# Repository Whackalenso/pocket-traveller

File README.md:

# Pocket Traveller

This is a Tamagotchi-inspired gadget to keep in your backpack, on your keychain, or in your pocket that encourages you to move more throughout your day.

The primary feature of the device is a screen that displays an avatar named Milo. Milo will walk when you walk, rest when you're idle, and sleep during long periods of inactivity. Milo will gain **XP** the more he moves, filling up a bar at the top of the screen. When this bar fills, Milo will gain a **level**. In addition to **level**, Milo will also become a **chud**, **plebian**, or **nomad** dependent on how much he has moved in the past few days. *Skip to [Interface Design and Art](#5-interface-design-and-art) for more details*

> *The name Milo comes from the famous ancient Greek athlete, Milo of Croton. Legend has it that he would lift a newborn ox on his shoulders every day, and as the ox grew bigger, so would he. In the same way, Milo's level and state is dependent on you, as if you were the ox.*

## Hardware

* **Raspberry Pi Pico** - The brain. Reads data from the motion sensor and controls the screen.
* **SH1106** - 1.3" OLED display.
* **ADXL345** - Accelerometer. Detects instantaneous acceleration that is used to estimate longer-term motion.
* **TPU4056** - Charger module. Provides the USB-C port for charging the battery.
* **3.7v 1000mAh Lipo Battery**

All electronic components are wired together on a perfboard which is housed inside of a 3D printed case.

## Process

### 1. Breadboard Proof of Concept

#### Hardware Testing
To begin, we connected the screen and motion sensor to the Pico on a breadboard to test whether they worked properly and to figure out how to interface with them. We had some trouble finding the correct address for interfacing with our motion sensor. We got it to work eventually but ended up having to replace the sensor because it was a knockoff.

#### Motion Data Classification Experiment
The next thing we needed to test is whether we could accurately classify data from the accelerometer into two states: idle and moving. This would be the core mechanism of the device, where everything else is just essentially an just interface to wrap around it. We knew this might be difficult because we chose our motion sensors to just be an accelerometer for simplicity, not an accelerometer + GPS combo. This means that the device has no reference for changes in position, only forces acted upon the device at each moment. 

After doing some research we learned that two qualities of the data can be measured in order to detect whether the user is moving: 

**Energy:** How strongly the device is moving. Measured as population variance of the magnitude of the force acted upon the sensor in a given window.<br>
**Rhythm:** How rhythmic the movements in the device are. Measured as how accurately a sequence of movements lines up with a shifted copy of itself.

The importance of this rhythm quality is that some movements may involve a lot of movement, such as shaking the device around or putting it into your backpack, however these movements shouldn't be classified as "moving". Actual "moving" scenarios, such as walking or running, will have a certain rhythm to it, as steps happen at a certain relative frequency.

Given all this, we needed to come up with thresholds for these two qualities in order to distinguish between moving and idle in a given time window. First, we made a sketch for the device that would simply display "IDLE" if the wearer is idle and "MOVING" if the wearer is moving. We played around with different values for the thresholds to see if we could create a result that seemed accurate. However, none of them seemed to work. So, abandoned trial and error and made a system to calibrate these thresholds:
1. Came up with a list of all possible movement scenarios that each give different kinds of data: sitting still, standing, fidgeting, slow walking, walking, running, and driving. Sitting still, standing, fidgeting, and driving would be classified as idle, while slow walking, walking, and running would be classified as moving. The hope/hypothesis was that there should be some value for both energy and rhythm that would separate one group from the other.
2. Created a Pico sketch for collecting energy and rhythm data
3. Recorded data for each scenario by performing the actions while holding the device
4. Created a Python script that plotted out all the data on a graph and automatically recommended thresholds for both qualities

*Recording running and driving data*

https://github.com/user-attachments/assets/422ddd09-90e0-466a-b9c1-0ad0e3300164

What we found was that the data reflected some of what we hoped: there is a clear distinction between the energy (variance) measured in "moving" states (shown in green) vs the energy measured in "idle" states. However, after looking at the graph on the right, we realized that rhythm was not necessary for distinguishing between moving and idle states, because the differences in energy alone already distinguished them. In addition, the recommended thresholds the script gave us were way off from what we observed in the graph. This didn't matter as much because we were able to look at the graph for ourselves and see where the line should be drawn, but it meant that something was off with our code and we would revisit it if needed.

We tried out our testing sketch again, but this time used 10^8 as our energy threshold and 0 for our rhythm threshold. This time, it was pretty reasonable at displaying "MOVING" when we moved with the device. However, since we weren't classifying the state with rhythm anymore, movements such as fidgeting shaking the device caused "MOVING" to be displayed as well. Our verdict was that this was good enough for now. As long as the device detects a moving state when the user is moving, it's ok that it doesn't perfectly detect and idle state. Random extra detected movement detected throughout the day will be insignificant compared to the actual long-term movement the user will actually do. The only downside is that the user may see the avatar on the screen move a little bit every now and then when they are just fidgeting with it. This will be something to revisit in the future when we have time to dive deeper into the calibration and data classification experiment.

#### Battery and Power States Proof of Concept

The next step was to test powering the device with a battery. There were a few new problems we needed to tackle:
Making sure the Pico doesn’t get damaged
Detecting that the device is being charged so that it can draw less power during this state and display a different screen
Adding a sleep state so that we can lengthen the battery life of the device without having an off button

After doing some research, we learned that routing the power from the battery through a schottkey diode was most optimal so that the charger module doesn’t get confused when detecting when the battery is full. We wired this up and the Pico didn’t blow up.

Next, we needed a way to detect whether the battery is currently being charged or not. Unfortunately, there was no dedicated pin for this on the TP4056 module. Our solution was to wire the input voltage signal– the voltage being received by the charging port– to a pin on the Pico. We had to use a voltage divider to transform this 5V signal into a 3.3V signal safe for the Pico. When this pin is read as high, we programmed the device to both draw less power (drawing power while charging the battery would confuse the charger module) and display “charging” text on the screen.

Finally, we programmed the device to go into “deep sleep” after a certain duration of inactivity. Because we chose to not have a power button on the device for simplicity, we needed a way for the device to turn off so that the battery doesn’t drain 24/7. This deep sleep state essentially powers off the Pico almost entirely. In order to wake the device up again, a special pin on the motion sensor that turns on when it detects motion can wake up the Pico even when it’s barely running.

### 3. Soldering Onto Perfboard

Now that the proof of concept was fleshed out, we could move on to soldering all the components into a more permanent and compact form that would be the innards of our final version. We began by creating a schematic in KiCad which was useful in guiding us to creating the most compact layout. Exact measurements were taken for each component to ensure our planned layout in the PCB editor was accurately spaced. This was important, especially making sure room was left for our wiring to run through the empty space in the board. Multiple wires and traces ran under components and through the back of the board, so any mistakes would be very hard to fix. Consequently, we made sure KiCad was referenced before soldering in any connections or components. Once everything was soldered in, we tested the code to make sure it ran properly. Much to our shock everything worked, so we taped down the battery to the board, trimmed the edges of the perfboard to get as compact of a design as possible and then moved on to designing the case. 

### 4. Designing a Case

Creating a case to house our circuit board was pretty straightforward:
* Measured all the components precisely with a caliper and/or looking at datasheets.
* Modeled the dimensions of the board and electronic components in CAD
* Modeled a box in two parts, the floor and everything else, to fit around the components. This included cutouts for the screen and USB port.
* Added a standoff on both the floor and box for one screw to screw from the floor through the circuit board into the box.
* Added fillets for aesthetics.
* Added tolerances for fit.
* Added a ring at the top so that the device can be used as a keychain

### 5. Interface Design and Art

There are four main features of the user interface that make up what this device is all about: the avatar, the level, the status, and the dialogues.

#### Avatar

The avatar is the defining feature of the device. It is an animation of Milo, our made up character. The drawing style is inspired by 16x16 pixel art Tamagotchi sprites. We drew each frame ourselves using pixel art software, then used a custom Python script, gen_sprites.py, to turn each image into data readable by the Pico, stored in sprites.h. For each status, there is an animation for resting and walking.

#### Level

The level is one of the two “movement-encouraging” features. It is is reflective of your total activity in the history of owning the device: it never goes down, only up. Whenever you move, you gain XP. Once you get a certain amount of XP, you will go up one level. Your level is displayed at the top of the screen. This XP value is hidden, however, a bar below the level indicator will fill up to reflect your progress towards the next level. Each level takes more and more XP to unlock, according to a formula such that level 10 is achievable in one week and level 100 is achievable in one year.

#### Status

The status is the second “movement-encouraging” feature. It is different from level in that it reflects how much you have been moving recently, as opposed to of all time. There are three statuses, “chud”, “pleb”, and “nomad”. The status indicator next to the level indicator will display one of these statuses depending on how much time in the past 72 hours you have spent moving. The current pace for each status are as follows:

Chud: <40 mins / day<br>
Pleb: ~1hr / day<br>
Nomad: >3hr / day

The threshold for promoting to a higher status is different than the threshold for demoting down to a lower rank so that sitting on the border between two statuses doesn’t cause weird issues. 

In addition to displaying your status at the top of the screen, Milo will also look different based on status:

| | Chud | Pleb | Nomad |
| :---: | :---:  | :---:  | :---:   |
| **Rest** | |  |  |
| **Walk** | |  |  |

#### Dialogues

The dialogues are a feature intended to add a little more whimsy, mystery, and sometimes encouragement to the device. After a long enough period of inactivity, picking up the device will cause text to pop up on the screen saying something about what Milo is doing or thinking about. These dialogues are stored in card_lines.h. Here are some examples:

*"milo is reading feminist literature"*<br>
*"milo is workshopping his memoir"*<br>
*"milo wants to go on a hike"*<br>
*"milo is getting into lifting to get over his boredom"*

Mostly these will just be jokes, however, they are intended to also subtly hint the user towards ways they can find more fulfillment in their own life. 

---

Made with ❤️ by Nigel Weiss and Brenden Cech

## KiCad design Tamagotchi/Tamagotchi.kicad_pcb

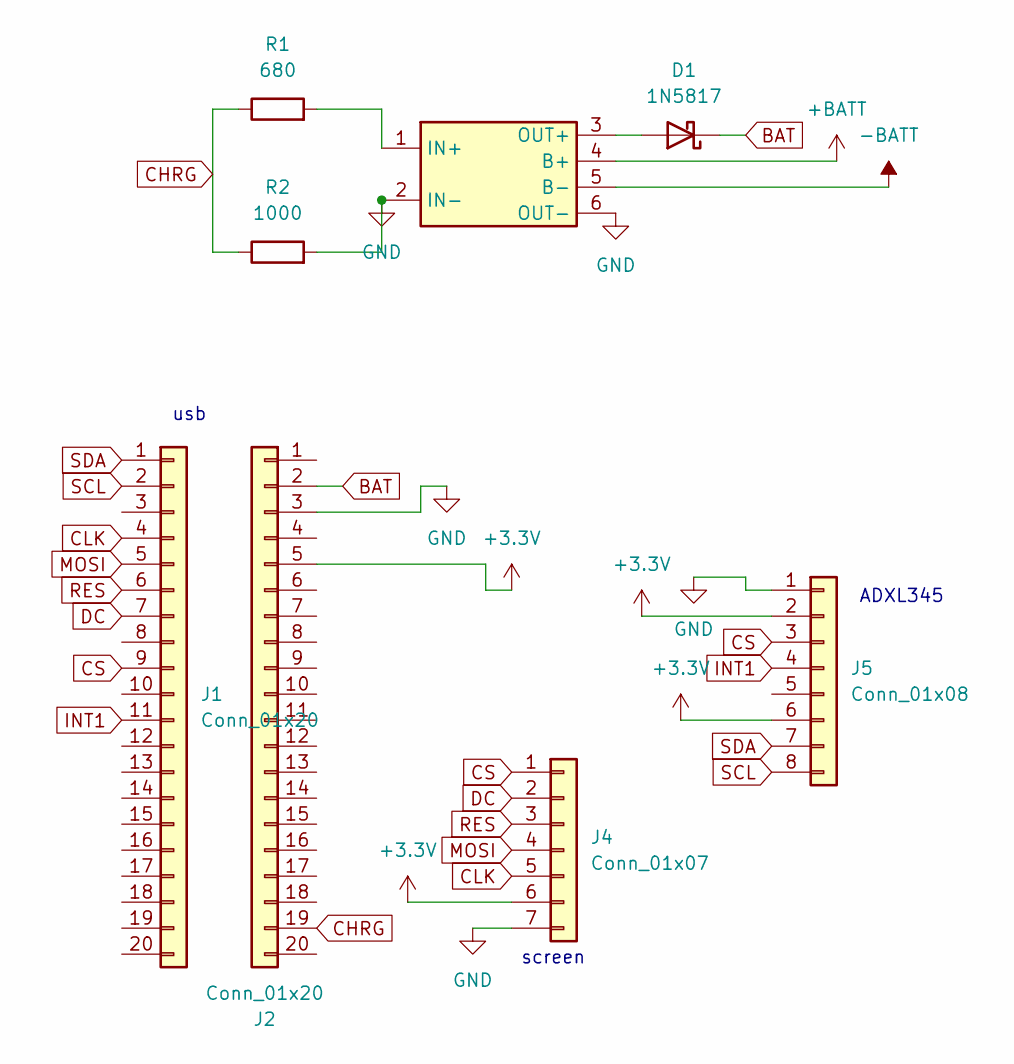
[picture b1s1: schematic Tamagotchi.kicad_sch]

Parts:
D1: 1N5817; D_DO-41_SOD81_P10.16mm_Horizontal
J1, J2: Conn_01x20; PinHeader_1x20_P2.54mm_Vertical
J4: Conn_01x07; Tama_Screen
J5: Conn_01x08; Tama_Sensor
R1: 680; R_0201_0603Metric
R2: 1000; R_0201_0603Metric
U1: TP4056-module; Tama_TP4056

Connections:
+3.3V: J2.5, J4.6, J5.2, J5.6
+BATT: U1.4 (B+)
-BATT: U1.5 (B-)
BAT: D1.1 (K), J2.2
CHRG: J2.19, R1.1, R2.1
CLK: J1.4, J4.5
CS: J1.9, J4.1, J5.3
DC: J1.7, J4.2
GND: J2.3, J4.7, J5.1, R2.2, U1.2 (IN-), U1.6 (OUT-)
INT1: J1.11, J5.4
MOSI: J1.5, J4.4
unnamed: D1.2 (A), U1.3 (OUT+)
unnamed: R1.2, U1.1 (IN+)
RES: J1.6, J4.3
SCL: J1.2, J5.8
SDA: J1.1, J5.7

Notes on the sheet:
screen
usb
ADXL345

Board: 2 copper layers, 8 parts (6 on the bottom side), 14 nets, no tracks yet.

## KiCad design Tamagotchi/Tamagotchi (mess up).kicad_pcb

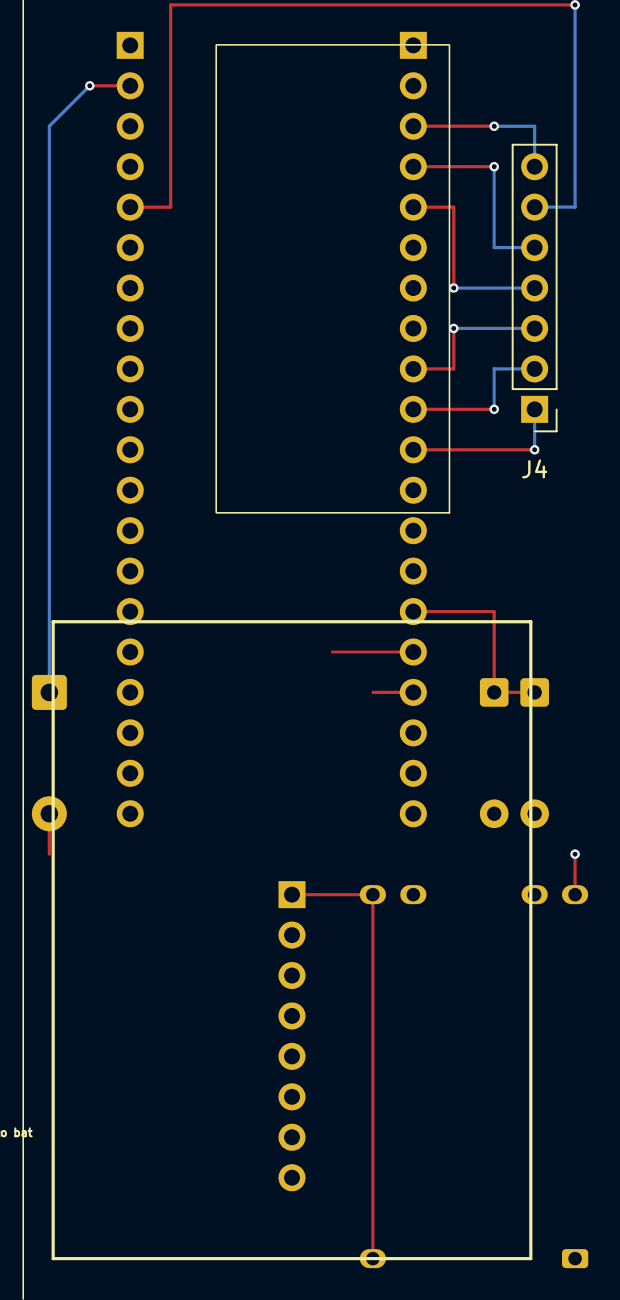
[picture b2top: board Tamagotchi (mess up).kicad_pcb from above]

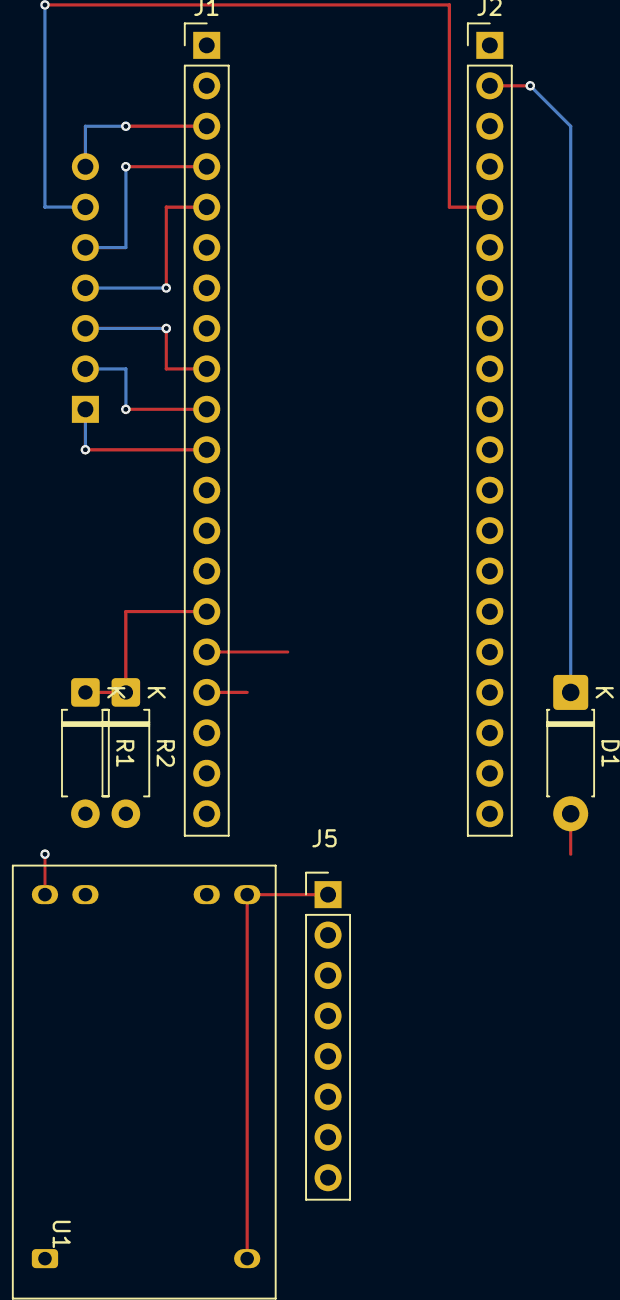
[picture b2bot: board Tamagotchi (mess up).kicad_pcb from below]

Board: 2 copper layers, 8 parts (7 on the bottom side), 14 nets.

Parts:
D1: 1N5817; D_DO-41_SOD81_P7.62mm_Horizontal
J1, J2: Conn_01x20; PinHeader_1x20_P2.54mm_Vertical
J4: Conn_01x07; Tama_Screen
J5: Conn_01x08; Tama_Sensor
R1: 680; D_A-405_P7.62mm_Horizontal
R2: 1000; D_A-405_P7.62mm_Horizontal
U1: TP4056-module; Tama_TP4056

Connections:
+3.3V: J2.5, J4.6, J5.2, J5.3, J5.6
BAT: D1.1 (K), J2.2
CHRG: J1.15, R1.1, R2.1
CLK: J1.4, J4.5
CS: J1.11, J4.1
DC: J1.10, J4.2
GND: J1.3, J1.8, J2.3, J4.7, J5.1, R2.2, U1.2 (IN-), U1.6 (OUT-)
INT1: J1.20, J5.4
MOSI: J1.5, J4.4
unnamed: D1.2 (A), U1.3 (OUT+)
unnamed: R1.2, U1.1 (IN+)
RES: J1.9, J4.3
SCL: J1.17, J5.8
SDA: J1.16, J5.7
